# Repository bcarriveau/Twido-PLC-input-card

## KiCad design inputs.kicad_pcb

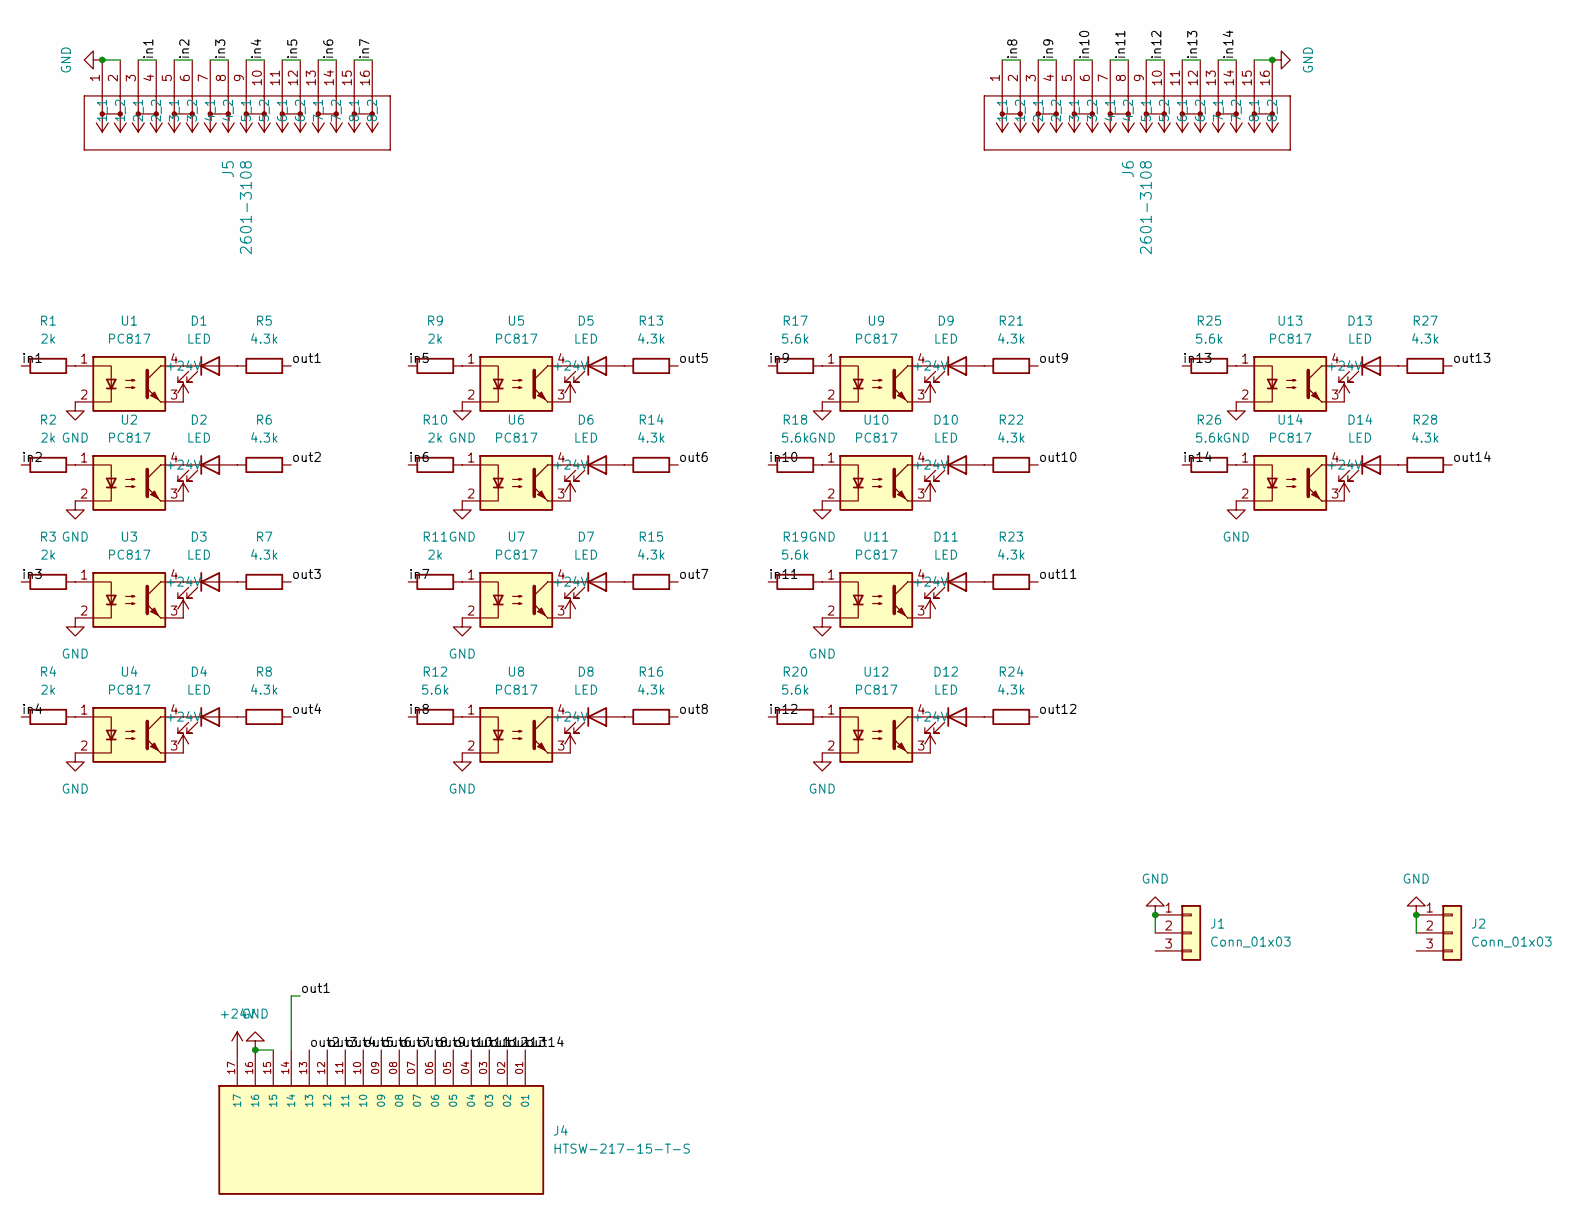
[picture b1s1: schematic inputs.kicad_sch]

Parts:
D1, D2, D3, D4, D5, D6, D7, D8, D9, D10, D11, D12, D13, D14: LED; LED_0805_2012Metric
J1, J2: Conn_01x03; PinHeader_1x03_P2.54mm_Vertical
J4: HTSW-217-15-T-S; SAMTEC_HTSW-217-15-T-S; PARTREV R
J5, J6: 2601-3108; CONN8_2601-3108_WAG
R1, R2, R3, R4, R9, R10, R11: 2k; R_0805_2012Metric
R5, R6, R7, R8, R13, R14, R15, R16, R21, R22, R23, R24, R27, R28: 4.3k; R_0805_2012Metric
R12, R17, R18, R19, R20, R25, R26: 5.6k; R_0805_2012Metric
U1, U2, U3, U4, U5, U6, U7, U8, U9, U10, U11, U12, U13, U14: PC817; DIP-4_W7.62mm

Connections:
+24V: J4.17, U1.3, U2.3, U3.3, U4.3, U5.3, U6.3, U7.3, U8.3, U9.3, U10.3, U11.3, U12.3, U13.3, U14.3
/in1: J5.3 (2_1), J5.4 (2_2), R1.2
/in2: J5.5 (3_1), J5.6 (3_2), R2.2
/in3: J5.7 (4_1), J5.8 (4_2), R3.2
/in4: J5.9 (5_1), J5.10 (5_2), R4.2
/in5: J5.11 (6_1), J5.12 (6_2), R9.2
/in6: J5.13 (7_1), J5.14 (7_2), R10.2
/in7: J5.15 (8_1), J5.16 (8_2), R11.2
/in8: J6.1 (1_1), J6.2 (1_2), R12.2
/in9: J6.3 (2_1), J6.4 (2_2), R17.2
/in10: J6.5 (3_1), J6.6 (3_2), R18.2
/in11: J6.7 (4_1), J6.8 (4_2), R19.2
/in12: J6.9 (5_1), J6.10 (5_2), R20.2
/in13: J6.11 (6_1), J6.12 (6_2), R25.2
/in14: J6.13 (7_1), J6.14 (7_2), R26.2
/out1: J4.14, R5.2
/out2: J4.13, R6.2
/out3: J4.12, R7.2
/out4: J4.11, R8.2
/out5: J4.10, R13.2
/out6: J4.09, R14.2
/out7: J4.08, R15.2
/out8: J4.07, R16.2
/out9: J4.06, R21.2
/out10: J4.05, R22.2
/out11: J4.04, R23.2
/out12: J4.03, R24.2
/out13: J4.02, R27.2
/out14: J4.01, R28.2
GND: J1.1, J1.2, J2.1, J2.2, J4.15, J4.16, J5.1 (1_1), J5.2 (1_2), J6.15 (8_1), J6.16 (8_2), U1.2, U2.2, U3.2, U4.2, U5.2, U6.2, U7.2, U8.2, U9.2, U10.2, U11.2, U12.2, U13.2, U14.2
unnamed: D1.2 (A), R5.1
unnamed: D1.1 (K), U1.4
unnamed: D2.2 (A), R6.1
unnamed: D2.1 (K), U2.4
unnamed: D3.2 (A), R7.1
unnamed: D3.1 (K), U3.4
unnamed: D4.2 (A), R8.1
unnamed: D4.1 (K), U4.4
unnamed: D5.2 (A), R13.1
unnamed: D5.1 (K), U5.4
unnamed: D6.2 (A), R14.1
unnamed: D6.1 (K), U6.4
unnamed: D7.2 (A), R15.1
unnamed: D7.1 (K), U7.4
unnamed: D8.2 (A), R16.1
unnamed: D8.1 (K), U8.4
unnamed: D9.2 (A), R21.1
unnamed: D9.1 (K), U9.4
unnamed: D10.2 (A), R22.1
unnamed: D10.1 (K), U10.4
unnamed: D11.2 (A), R23.1
unnamed: D11.1 (K), U11.4
unnamed: D12.2 (A), R24.1
unnamed: D12.1 (K), U12.4
unnamed: D13.2 (A), R27.1
unnamed: D13.1 (K), U13.4
unnamed: D14.2 (A), R28.1
unnamed: D14.1 (K), U14.4
unnamed: R1.1, U1.1
unnamed: R2.1, U2.1
unnamed: R3.1, U3.1
unnamed: R4.1, U4.1
unnamed: R9.1, U5.1
unnamed: R10.1, U6.1
unnamed: R11.1, U7.1
unnamed: R12.1, U8.1
unnamed: R17.1, U9.1
unnamed: R18.1, U10.1
unnamed: R19.1, U11.1
unnamed: R20.1, U12.1
unnamed: R25.1, U13.1
unnamed: R26.1, U14.1

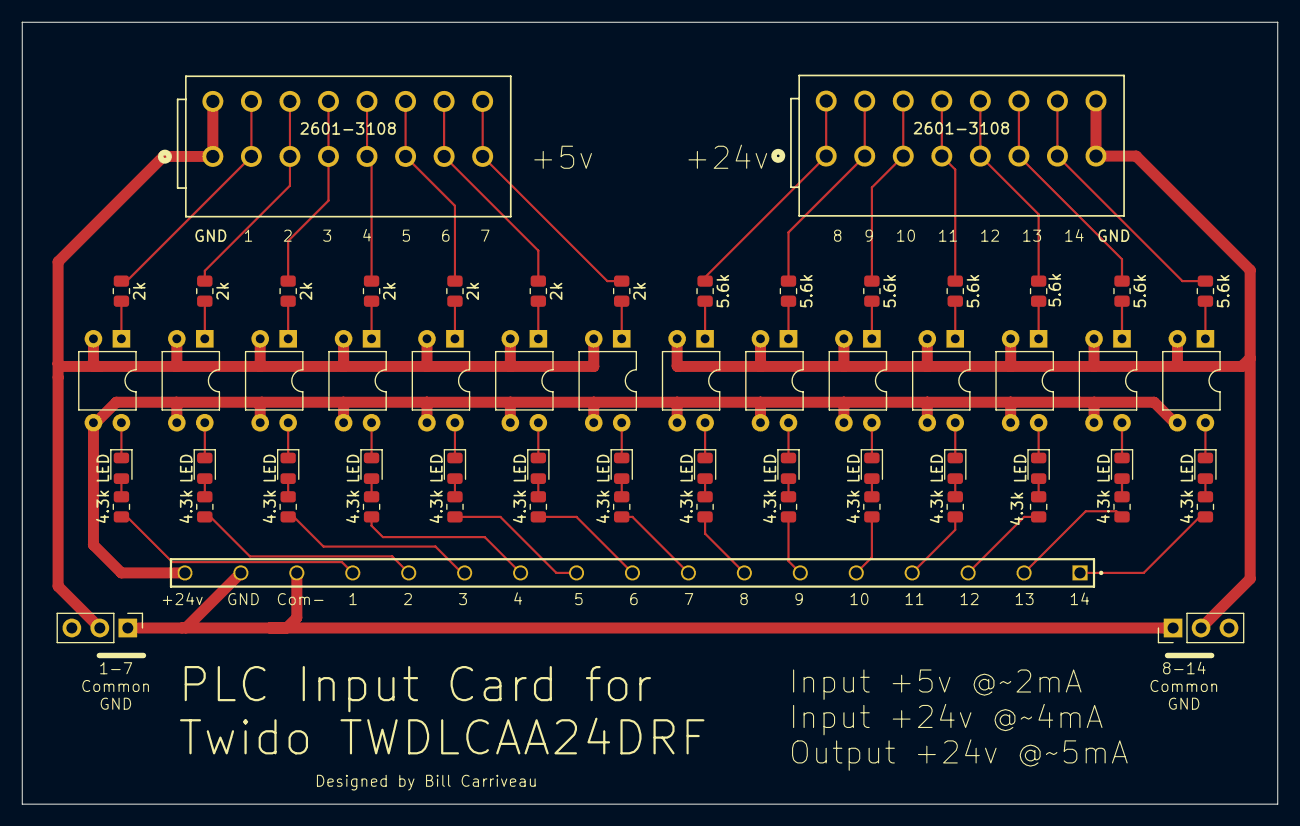
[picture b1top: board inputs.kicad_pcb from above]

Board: 2 copper layers, 114.0 x 71.0 mm, 61 parts (0 on the bottom side), 72 nets.

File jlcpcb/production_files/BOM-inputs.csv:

Comment,Designator,Footprint,LCSC,Quantity
2k,"R1,R10,R11,R2,R3,R4,R9",R_0805_2012Metric,C17604,7
4.3k,"R13,R14,R15,R16,R21,R22,R23,R24,R27,R28,R5,R6,R7,R8",R_0805_2012Metric,C17667,14
5.6k,"R12,R17,R18,R19,R20,R25,R26",R_0805_2012Metric,C4382,7
LED,"D1,D10,D11,D12,D13,D14,D2,D3,D4,D5,D6,D7,D8,D9",LED_0805_2012Metric,C84256,14
PC817,"U1,U10,U11,U12,U13,U14,U2,U3,U4,U5,U6,U7,U8,U9",DIP-4_W7.62mm,C96006,14
HTSW-217-15-T-S,J4,SAMTEC_HTSW-217-15-T-S,,1
2601-3108,J5,CONN8_2601-3108_WAG,,1
2601-3108,J6,CONN8_2601-3108_WAG,,1
Conn_01x03,J2,PinHeader_1x03_P2.54mm_Vertical,,1
Conn_01x03,J1,PinHeader_1x03_P2.54mm_Vertical,,1

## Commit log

2025-04-04 Move to 2 8Pin Wagos
2025-04-05 Add Common GND Jumpers, split 5v/24v, Add LEDS
2025-04-06 update Silkscreen, update values
    First board ordered
